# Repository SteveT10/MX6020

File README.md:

# MX60 + 20

The MX60 + 20 is a 60% keyboard PCB that features Hot-Swappable MX Switches, RGB underglow, RGB backlighting, and a dettachable 4x5 macropad via micro-usb male to male. The hardware was designed in Kicad by myself and uses QMK firwmare.

## Design Specifications:
Main body:
- Modified ANSI 60% layout
    - Shrank 2.25u shift down to 2u shift key.
    - Extra 1u key added on second to bottom row.
    - 64 Keys total.
- 8 WS2812 ARGBs for underglow
- 64 RGB Backlights
- USB-C Connecter to PC.
- Micro-USB Connecter to macropad.
- 288.8 mm by 104 mm PCB size.
- 2 Layer PCB

Front side of main body PCB.

Back side of main body PCB.

Macropad:
- 4x5 layout
    - 20 keys total.
- 4 WS2812 ARGBs for underglow.
- 20 RGB backlights.
- USB-C Connecter to PC.
- Micro-USB Connecter to main body.
- 79 mm by 104 mm PCB size.
- 2 Layer PCB

Front side of macro pad PCB.

Back side of macro pad PCB.

## Goal
This project's overall goal is to act as a progressive learning project that complements my education in Computer Engineering. The first goal of this project was to familiarize myself with hardware design, where I would learn: 
- How to design circuit schematics and PCB layout in EDA software, specifically KiCad.
- How to use 3D printers and CAD software to design keycaps and cases
- How to use tools such reflow ovens, stencils, and soldering paste to assemble electronics.

<p>After verifying my hardware design and solving any potential issues, I would move onto the second goal of this project which is learn more about firmware, more specifically:</p>

- How to program C/Assembly in ARM-based MCU.
- How communication protocals such as I2C are implemented.
- More to come! (As I have not gotten to this stage yet)

## Creating Gerbers
Most PCB fabrication places expect gerber files. Gerber files describe the layout of pads, traces, drill holes, and other geometry for each layer on the PCB. Gerber files should be uploaded in a compress zip file containing all layers. To create gerber files in KiCad v7.0:

1. Open KiCad's PCB viewer
2. Go to `File` -> `Plot`
3. Select layers and options accordingly to your fabrication shop's settings. I chose JLCPCB so I set the following options below and set all others to unchecked.
    * Include Layers:
        * F.Cu
        * B.Cu
        * F.Paste
        * B.Paste
        * F.Silkscreen
        * B.Silkscreen
        * F.Mask
        * B.Mask
        * Edge.cuts
    * `Plot reference designators`
    * `Plot footprint values`
    * `Use Protel filename extensions`
    * `Subtract soldermask from silkscreen`
    * Check zone fills before plotting.
4. Set the output directory to `project-name-gerbers`, where project name is a placeholder.
5. Click `Plot` to generate layer gerbers.
6. Click `Generate Drill files...`
7. Again, select options that match with your fabrication shop's specifications. For JLCPCB, this is:
    * Drill File Format set to Excellon.
    * Oval Holes Drill Mode is set to `Use alternate drill mode`
    * Map File Format set to `Gerber`
    * Drill Origin set to `Absolute`
    * Drill units set to `Millimeters`
    * Zeros format set to `Decimal format`
8. Click `Generate Drill File`
9. Zip up your gerber files and now it is ready for upload.

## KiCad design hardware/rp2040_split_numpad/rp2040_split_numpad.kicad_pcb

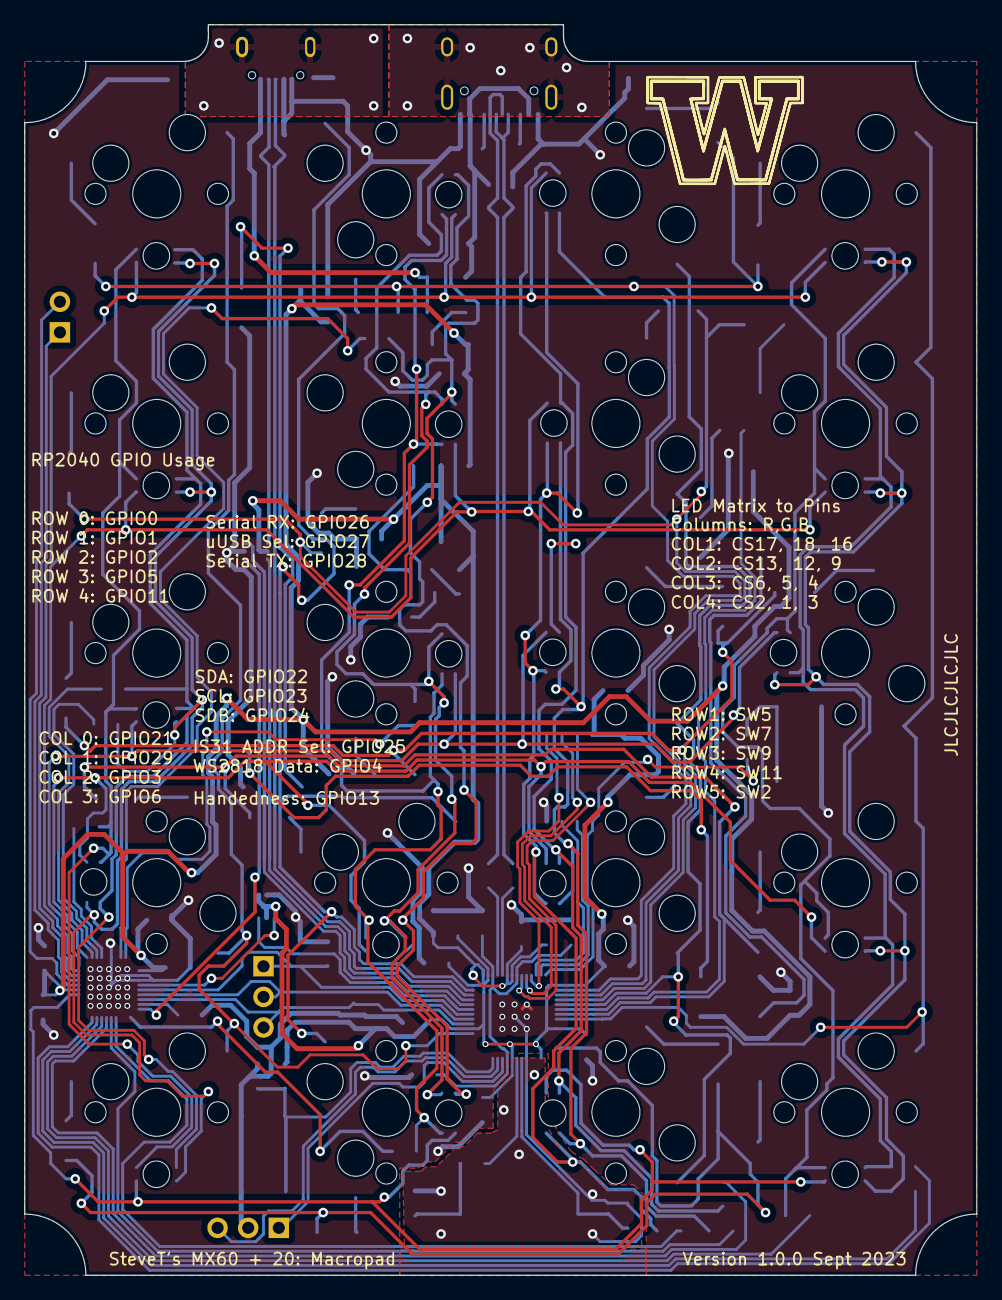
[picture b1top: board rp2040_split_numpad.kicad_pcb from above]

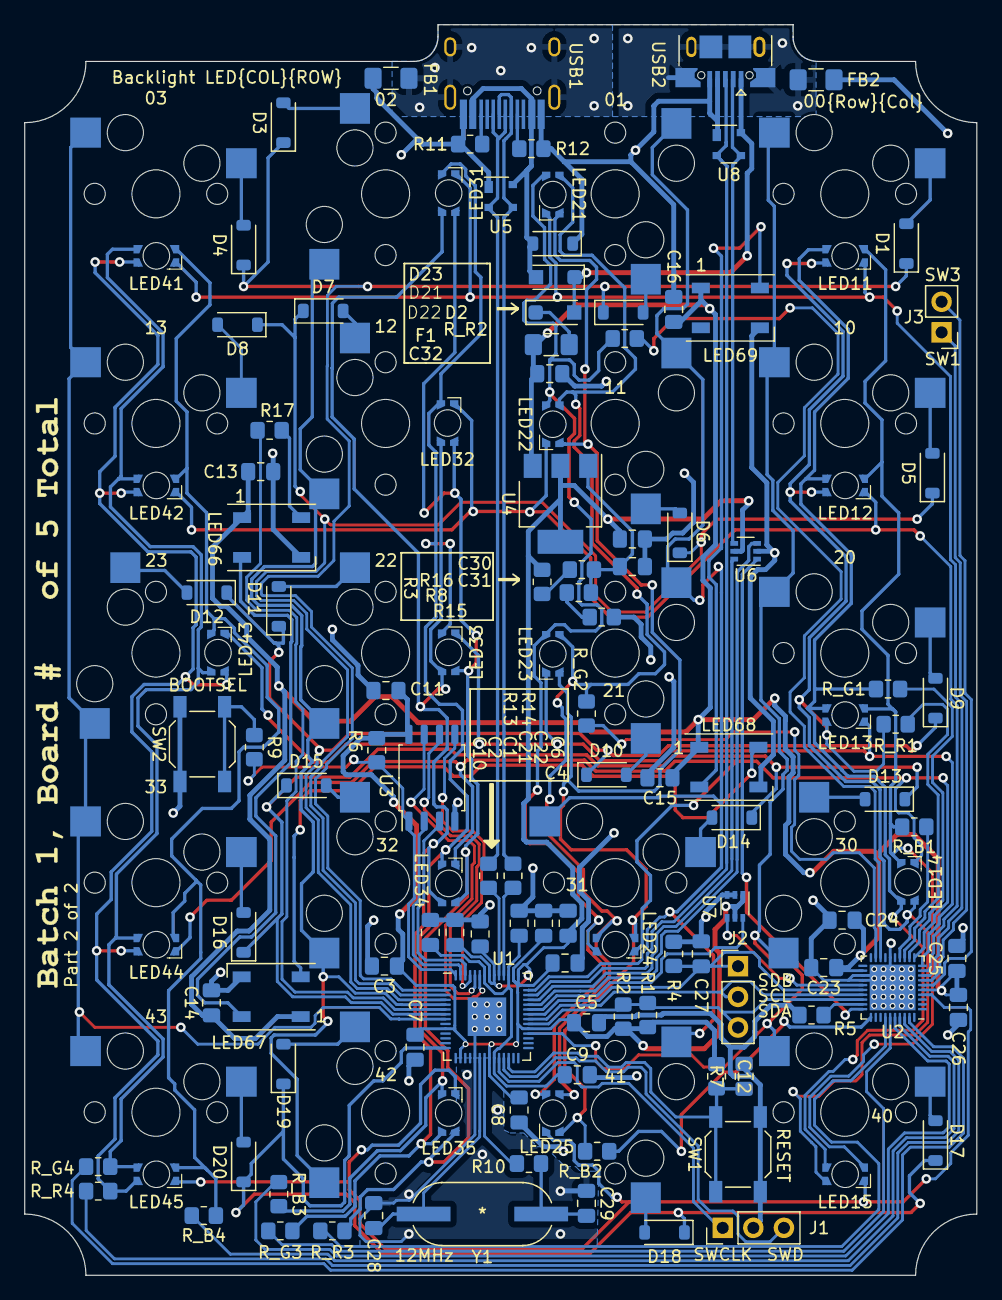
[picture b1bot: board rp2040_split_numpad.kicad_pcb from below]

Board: 2 copper layers, 79.0 x 103.8 mm, 143 parts (123 on the bottom side), 107 nets.

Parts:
C1, C2, C3, C4, C5, C6, C7, C8, C9, C10, C11, C12, C13, C14, C15, C16: 100n; C_0805_2012Metric_Pad1.18x1.45mm_HandSolder
C21, C22, C23, C24: 1u; C_0805_2012Metric_Pad1.18x1.45mm_HandSolder
C25, C26, C27: 0.1u; C_0805_2012Metric_Pad1.18x1.45mm_HandSolder
C28, C29: 27p; C_0805_2012Metric_Pad1.18x1.45mm_HandSolder
C30, C31, C32: 10u; C_0805_2012Metric_Pad1.18x1.45mm_HandSolder
D1, D2, D3, D4, D5, D6, D7, D8, D9, D10, D11, D12, D13, D14, D15, D16, D17, D18, D19, D20: D_Small; D_SOD-123
D21, D22: D_Schottky; D_SOD-123FL
D23: D_TVS; D_SOD-123
F1: 500m; Fuse_1206_3216Metric_Pad1.42x1.75mm_HandSolder
FB1, FB2: 60@100Mhz; L_1206_3216Metric_Pad1.42x1.75mm_HandSolder
J1, J2: Conn_01x03; PinHeader_1x03_P2.54mm_Vertical
J3: Conn_01x02; PinHeader_1x02_P2.54mm_Vertical
K1: 00; MXOnly-1U-Hotswap
K2: 01; MXOnly-1U-Hotswap
K3: 02; MXOnly-1U-Hotswap
K4: 03; MXOnly-1U-Hotswap
K5: 10; MXOnly-1U-Hotswap
K6: 11; MXOnly-1U-Hotswap
K7: 12; MXOnly-1U-Hotswap
K8: 13; MXOnly-1U-Hotswap
K9: 20; MXOnly-1U-Hotswap
K10: 21; MXOnly-1U-Hotswap
K11: 22; MXOnly-1U-Hotswap
K12: 23; MXOnly-1U-Hotswap
K13: 30; MXOnly-1U-Hotswap
K14: 31; MXOnly-1U-Hotswap
K15: 32; MXOnly-1U-Hotswap
K16: 33; MXOnly-1U-Hotswap
K17: 40; MXOnly-1U-Hotswap
K18: 41; MXOnly-1U-Hotswap
K19: 42; MXOnly-1U-Hotswap
K20: 43; MXOnly-1U-Hotswap
LED11, LED12, LED13, LED14, LED15, LED21, LED22, LED23, LED24, LED25, LED31, LED32, LED33, LED34, LED35, LED41, LED42, LED43, LED44, LED45: LED_RAGB; LED__RBG_1206_3216Metric_ReverseMount_Hole2.2x2.2mm
LED66, LED67, LED68, LED69: WS2812B; LED_WS2812B_PLCC4_5.0x5.0mm_P3.2mm
R1, R2, R3: 2k; R_0805_2012Metric_Pad1.20x1.40mm_HandSolder
R4: 100k; R_0805_2012Metric_Pad1.20x1.40mm_HandSolder
R5, R6, R7: 10k; R_0805_2012Metric_Pad1.20x1.40mm_HandSolder
R8, R9, R10: 1k; R_0805_2012Metric_Pad1.20x1.40mm_HandSolder
R11, R12: 5.1k; R_0805_2012Metric_Pad1.20x1.40mm_HandSolder
R13, R14: 27; R_0805_2012Metric_Pad1.20x1.40mm_HandSolder
R15, R16, R17: 500; R_0805_2012Metric_Pad1.20x1.40mm_HandSolder
R_B1, R_B2, R_B3, R_B4: 20; R_0805_2012Metric_Pad1.20x1.40mm_HandSolder
R_G1, R_G2, R_G3, R_G4: 20; R_0805_2012Metric_Pad1.20x1.40mm_HandSolder
R_R1, R_R2, R_R3, R_R4: 51; R_0805_2012Metric_Pad1.20x1.40mm_HandSolder
SW1: Reset; SW_SPST_SKQG_WithStem
SW2: Boot; SW_SPST_SKQG_WithStem
U1: RP2040; QFN-56-1EP_7x7mm_P0.4mm_EP3.2x3.2mm
U2: IS31FL3743A-QULS4-TR; UQFN-40-1EP_5x5mm_P0.4mm_EP3.8x3.8mm
U3: W25Q32JVSS; SOIC-8_5.23x5.23mm_P1.27mm
U4: NCP1117-ADJ_SOT223; SOT-223-3_TabPin2
U5, U8: PRTR5V0U2X; SOT-143
U6, U7: BL1551B; SOT-363_SC-70-6
USB1: HRO-TYPE-C-31-M-12; HRO-TYPE-C-31-M-12-HandSoldering
USB2: USB_B_Micro; USB_Micro-B_XKB_U254-051T-4BH83-F1S
Y1: 12MHz; ABLS-12.000MHZ-B4-T

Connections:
+1V1: C9.1, C10.1, C21.1, U1.23 (DVDD), U1.45 (VREG_VOUT), U1.50 (DVDD)
+3.3V: C1.1, C2.1, C3.1, C4.1, C5.1, C6.1, C7.1, C8.1, C11.1, C22.1, C30.1, R1.1, R2.1, R3.1, R6.1, R7.1, U1.1 (IOVDD), U1.10 (IOVDD), U1.16 (GPIO13), U1.22 (IOVDD), U1.33 (IOVDD), U1.42 (IOVDD), U1.43 (ADC_AVDD), U1.44 (VREG_IN), U1.48 (USB_VDD), U1.49 (IOVDD), U3.8 (VCC), U4.2 (VO), U6.5 (V+), U7.1, U7.5 (V+)
+5V: C13.1, C14.1, C15.1, C16.1, C23.1, C24.1, C25.1, C26.1, C32.1, F1.2, LED66.1 (VDD), LED67.1 (VDD), LED68.1 (VDD), LED69.1 (VDD), U2.5 (PVCC), U2.22 (VCC), U4.3 (VI)
ADDR1: U2.25 (ADDR1), U7.4
ADDR_SEL: U1.37 (GPIO25), U7.6
BLUE1: R_B1.1, U2.14 (CS16)
BLUE2: R_B2.1, U2.31 (CS9)
BLUE3: R_B3.1, U2.36 (CS4)
BLUE4: R_B4.1, U2.37 (CS3)
COL0: K1.2, K5.2, K9.2, K13.2, K17.2, U1.32 (GPIO21)
COL1: K2.2, K6.2, K10.2, K14.2, K18.2, U1.41 (GPIO29_ADC3)
COL2: K3.2, K7.2, K11.2, K15.2, K19.2, U1.5 (GPIO3)
COL3: K4.2, K8.2, K12.2, K16.2, K20.2, U1.8 (GPIO6)
D+: R13.2, U5.2 (I/O1), USB1.6 (DP1), USB1.8 (DP2)
D-: R14.1, U5.3 (I/O2), USB1.5 (DN2), USB1.7 (DN1)
Earth: FB1.1, USB1.13 (SHIELD)
GND: C1.2, C2.2, C3.2, C4.2, C5.2, C6.2, C7.2, C8.2, C9.2, C10.2, C11.2, C12.2, C13.2, C14.2, C15.2, C16.2, C21.2, C22.2, C23.2, C24.2, C25.2, C26.2, C27.2, C28.1, C29.1, C30.2, C31.2, C32.2, D23.1 (A1), FB1.2, FB2.2, J1.2, LED66.3 (VSS), LED67.3 (VSS), LED68.3 (VSS), LED69.3 (VSS), R4.2, R5.2, R11.2, R12.2, R15.2, SW1.2, SW2.1, U1.19 (TESTEN), U1.57 (GND), U2.16 (PGND), U2.23 (AGND), U2.24 (ADDR2), U2.41 (Thermal), U3.4 (GND), U5.1 (GND), U6.2 (GND), U7.2 (GND), U7.3, U8.1 (GND), USB1.1 (GND), USB1.12 (GND), USB2.4 (ID), USB2.5 (GND)
GND1: FB2.1, USB2.6 (Shield)
GREEN1: R_G1.1, U2.12 (CS18)
GREEN2: R_G2.1, U2.19 (CS12)
GREEN3: R_G3.1, U2.35 (CS5)
GREEN4: R_G4.1, U2.39 (CS1)
LED_ROW1: LED11.2 (A), LED21.2 (A), LED31.2 (A), LED41.2 (A), U2.8 (SW5)
LED_ROW2: LED12.2 (A), LED22.2 (A), LED32.2 (A), LED42.2 (A), U2.9 (SW7)
LED_ROW3: LED13.2 (A), LED23.2 (A), LED33.2 (A), LED43.2 (A), U2.10 (SW9)
LED_ROW4: LED14.2 (A), LED24.2 (A), LED34.2 (A), LED44.2 (A), U2.11 (SW11)
LED_ROW5: LED15.2 (A), LED25.2 (A), LED35.2 (A), LED45.2 (A), U2.4 (SW2)
unnamed: C29.2, R10.1, Y1.1
unnamed: D1.2 (A), K1.1
unnamed: D2.2 (A), K2.1
unnamed: D3.2 (A), K3.1
unnamed: D4.2 (A), K4.1
unnamed: D5.2 (A), K5.1
unnamed: D6.2 (A), K6.1
unnamed: D7.2 (A), K7.1
unnamed: D8.2 (A), K8.1
unnamed: D9.2 (A), K9.1
unnamed: D10.2 (A), K10.1
unnamed: D11.2 (A), K11.1
unnamed: D12.2 (A), K12.1
unnamed: D13.2 (A), K13.1
unnamed: D14.2 (A), K14.1
unnamed: D15.2 (A), K15.1
unnamed: D16.2 (A), K16.1
unnamed: D17.2 (A), K17.1
unnamed: D18.2 (A), K18.1
unnamed: D19.2 (A), K19.1
unnamed: D20.2 (A), K20.1
unnamed: D22.1 (K), F1.1
unnamed: J3.1, U2.7 (SW3)
unnamed: J3.2, U2.6 (SW1)
unnamed: LED11.4 (BK), LED12.4 (BK), LED13.4 (BK), LED14.4 (BK), LED15.4 (BK), R_B1.2
unnamed: LED11.3 (GK), LED12.3 (GK), LED13.3 (GK), LED14.3 (GK), LED15.3 (GK), R_G1.2
unnamed: LED11.1 (RK), LED12.1 (RK), LED13.1 (RK), LED14.1 (RK), LED15.1 (RK), R_R1.2
unnamed: LED21.4 (BK), LED22.4 (BK), LED23.4 (BK), LED24.4 (BK), LED25.4 (BK), R_B2.2
unnamed: LED21.3 (GK), LED22.3 (GK), LED23.3 (GK), LED24.3 (GK), LED25.3 (GK), R_G2.2
unnamed: LED21.1 (RK), LED22.1 (RK), LED23.1 (RK), LED24.1 (RK), LED25.1 (RK), R_R2.2
unnamed: LED31.4 (BK), LED32.4 (BK), LED33.4 (BK), LED34.4 (BK), LED35.4 (BK), R_B3.2
unnamed: LED31.3 (GK), LED32.3 (GK), LED33.3 (GK), LED34.3 (GK), LED35.3 (GK), R_G3.2
unnamed: LED31.1 (RK), LED32.1 (RK), LED33.1 (RK), LED34.1 (RK), LED35.1 (RK), R_R3.2
unnamed: LED41.4 (BK), LED42.4 (BK), LED43.4 (BK), LED44.4 (BK), LED45.4 (BK), R_B4.2
unnamed: LED41.3 (GK), LED42.3 (GK), LED43.3 (GK), LED44.3 (GK), LED45.3 (GK), R_G4.2
unnamed: LED41.1 (RK), LED42.1 (RK), LED43.1 (RK), LED44.1 (RK), LED45.1 (RK), R_R4.2
unnamed: LED66.4 (DIN), R17.1
unnamed: LED66.2 (DOUT), LED67.4 (DIN)
unnamed: LED67.2 (DOUT), LED68.4 (DIN)
unnamed: LED68.2 (DOUT), LED69.4 (DIN)
unnamed: R9.1, SW2.2
unnamed: R8.2, R15.1
unnamed: R3.2, R16.1
unnamed: R5.1, U2.29 (ISET)
unnamed: C31.1, R8.1, R16.2, U4.1 (ADJ)
unnamed: R12.1, USB1.4 (CC1)
unnamed: R11.1, USB1.10 (CC2)
QSPI_CLK: U1.52 (QSPI_SCLK), U3.6 (CLK)
QSPI_SD1: U1.55 (QSPI_SD1), U3.2 (DO(IO1))
QSPI_SD2: U1.54 (QSPI_SD2), U3.3 (IO2)
QSPI_SD3: U1.51 (QSPI_SD3), U3.7 (IO3)
QSPI_SDO: U1.53 (QSPI_SD0), U3.5 (DI(IO0))
QSPI_SS: R6.2, R9.2, U1.56 (QSPI_SS), U3.1 (~CS)
RED1: R_R1.1, U2.13 (CS17)
RED2: R_R2.1, U2.18 (CS13)
RED3: R_R3.1, U2.34 (CS6)
RED4: R_R4.1, U2.38 (CS2)
RGB_DI: R17.2, U1.6 (GPIO4)
ROW0: D1.1 (K), D2.1 (K), D3.1 (K), D4.1 (K), U1.2 (GPIO0)
ROW1: D5.1 (K), D6.1 (K), D7.1 (K), D8.1 (K), U1.3 (GPIO1)
ROW2: D9.1 (K), D10.1 (K), D11.1 (K), D12.1 (K), U1.4 (GPIO2)
ROW3: D13.1 (K), D14.1 (K), D15.1 (K), D16.1 (K), U1.7 (GPIO5)
ROW4: D17.1 (K), D18.1 (K), D19.1 (K), D20.1 (K), U1.14 (GPIO11)
Reset: C12.1, R7.2, SW1.1, U1.26 (RUN)
SCL: J2.2, U1.35 (GPIO23), U2.27 (SCL)
SDA: J2.3, R1.2, R2.2, U1.34 (GPIO22), U2.28 (SDA)
SDB: C27.1, J2.1, R4.1, U1.36 (GPIO24), U2.26 (SDB)
SERIAL_RX: U1.38 (GPIO26_ADC0), U6.3
SWCLK: J1.1, U1.24 (SWCLK)
SWD: J1.3, U1.25 (SWD)
SYNC: U2.30 (SYNC), U6.1
USB_DM: R14.2, U1.46 (USB_DM)
USB_DP: R13.1, U1.47 (USB_DP)
VCC: D21.2 (A), D23.2 (A2), U5.4 (VCC), USB1.2 (VBUS), USB1.11 (VBUS)
VSYS: D21.1 (K), D22.2 (A), U8.4 (VCC), USB2.1 (VBUS)
XIN: C28.2, U1.20 (XIN), Y1.2
XOUT: R10.2, U1.21 (XOUT)
uUSB_D+: U1.40 (GPIO28_ADC2), U8.2 (I/O1), USB2.3 (D+)
uUSB_D-: U6.4, U8.3 (I/O2), USB2.2 (D-)
uUSB_SEL: U1.39 (GPIO27_ADC1), U6.6

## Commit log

2023-10-27 First commit: KiCad Files, README, media images
2023-11-07 Updated README Images
2023-12-18 Fixed Vreg circuit and silkscreen

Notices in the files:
parts and their libraries:
Copyright 2021 Accelerated Designs. All rights reserved.
